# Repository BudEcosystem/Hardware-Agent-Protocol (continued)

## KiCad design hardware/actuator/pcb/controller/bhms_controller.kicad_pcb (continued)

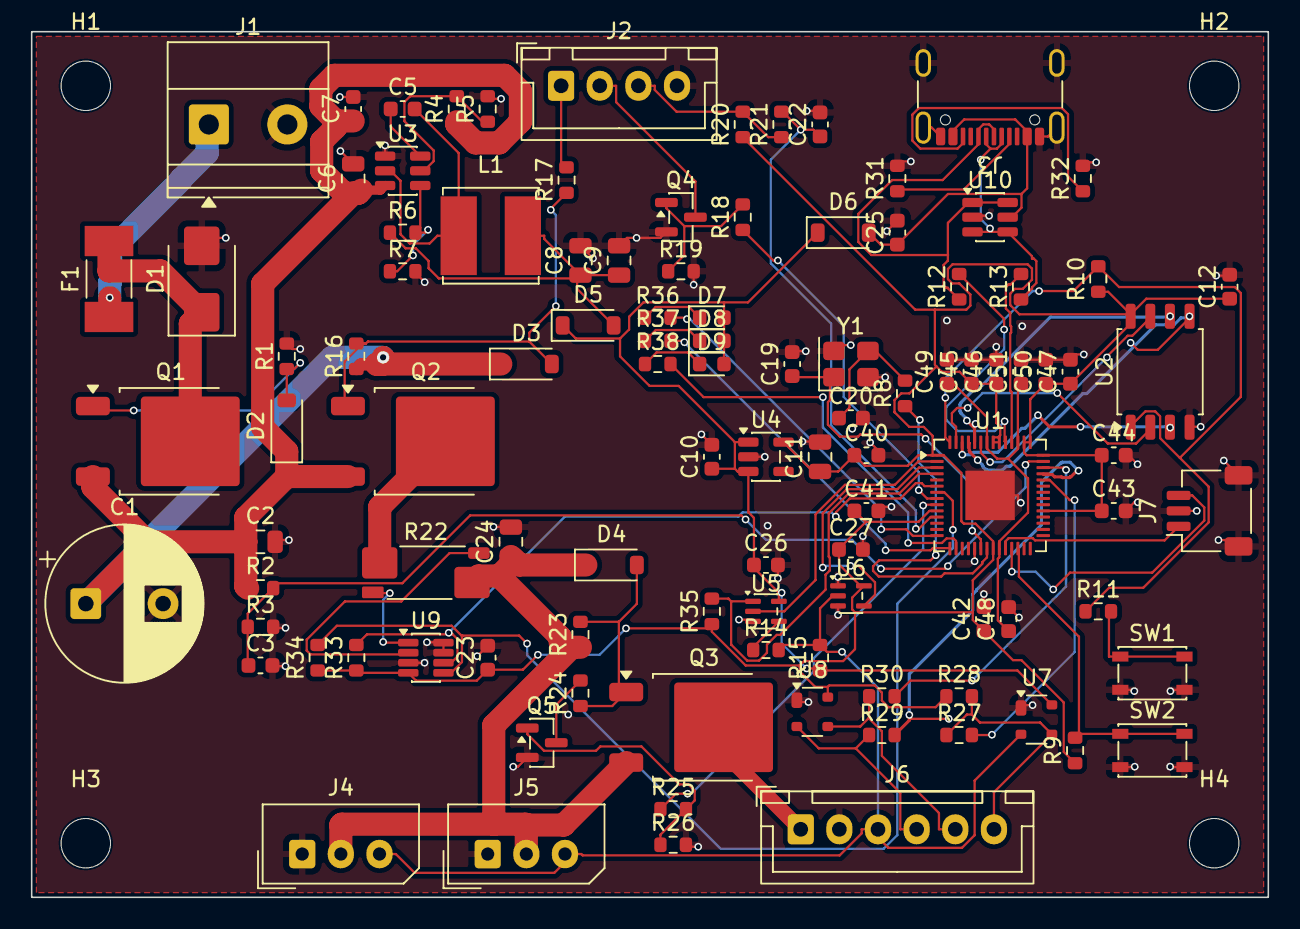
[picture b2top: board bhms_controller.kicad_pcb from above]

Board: 2 copper layers, 80.0 x 56.0 mm, 109 parts (0 on the bottom side), 69 nets.

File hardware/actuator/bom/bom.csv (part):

section,item,manufacturer,mpn,qty,unit_usd,ext_usd,price_source,notes
Arm,"Serial bus servo 12 V, 30 kg.cm, 4096-count magnetic encoder",Feetech,"STS3215 (12 V, C018 1:345)",5,18.0,90.0,"estimate (typical 2026 distributor price, not a quote)",IDs 1-5; variant code to confirm with supplier at order time
Arm,Deep-groove ball bearing 8x22x7,generic (e.g. SKF),608-2RS,4,0.5,2.0,"estimate (typical 2026 distributor price, not a quote)",shoulder and elbow shafts
Arm,"Shoulder pinion, machined steel (C45), 17T module 1.5, 14 mm face, 4 x M2 on a 14 mm circle (CNC service, drawing = cad/out/pinion_shoulder.step, committed)",CNC service (custom),cad/out/pinion_shoulder.step (committed; regenerate: python cad/build.py),1,18.0,18.0,"estimate (typical 2026 distributor price, not a quote)","ESTIMATE of a one-off turned and milled part; replaces the printed pinion (stress, design.md section 4)"
Arm,Deep-groove ball bearing 4x13x5,generic (e.g. SKF),624-2RS,3,0.6,1.8,"estimate (typical 2026 distributor price, not a quote)","2 pinion supports, wrist idler"
Arm,Deep-groove ball bearing 30x42x7,generic (e.g. SKF),6806-2RS,1,3.0,3.0,"estimate (typical 2026 distributor price, not a quote)",yaw turntable
Arm,"Hex bolt M8x70, partial thread, 8.8, zinc",generic,ISO 4014 M8x70,2,0.4,0.8,"estimate (typical 2026 distributor price, not a quote)",shoulder/elbow shafts
Arm,Nyloc nut M8,generic,ISO 10511 M8,2,0.08,0.16,"estimate (typical 2026 distributor price, not a quote)",
Arm,Washer M8 (16 mm OD),generic,ISO 7089 M8,4,0.03,0.12,"estimate (typical 2026 distributor price, not a quote)",bear on the 608 inner races only
Arm,Socket head cap screw M4x12,generic,ISO 4762 M4x12,6,0.06,0.36,"estimate (typical 2026 distributor price, not a quote)","2 pinion supports, 4 shell-to-plate"
Arm,Socket head cap screw M4x16 + nyloc nut,generic,ISO 4762 M4x16 / ISO 10511 M4,1,0.12,0.12,"estimate (typical 2026 distributor price, not a quote)",wrist idler
Arm,Washer M4 (9 mm OD),generic,ISO 7089 M4,4,0.02,0.08,"estimate (typical 2026 distributor price, not a quote)",inner-race spacers
Arm,Heat-set insert M4 x 6,generic (e.g. Ruthex),M4x8.1 RX-M4x8.1,6,0.1,0.6,"estimate (typical 2026 distributor price, not a quote)","pinion stubs, shell bosses"
Arm,Heat-set insert M3 x 5.7,generic (e.g. Ruthex),RX-M3x5.7,32,0.06,1.92,"estimate (typical 2026 distributor price, not a quote)","servo lids (5), pod lid, PCB"
Arm,Socket head cap screw M3x8,generic,ISO 4762 M3x8,32,0.04,1.28,"estimate (typical 2026 distributor price, not a quote)",
Arm,Pan head screw M2x8 (servo horn),generic,ISO 7045 M2x8,20,0.03,0.6,"estimate (typical 2026 distributor price, not a quote)","turret, pinions, wrist, flange"
Arm,"Ball spring plunger M5, 3 mm ball, stainless",generic,select at order (M5 x 12 class),1,1.5,1.5,"estimate (typical 2026 distributor price, not a quote)",bayonet detent; MPN not fixed
Arm,Heat-set insert M5,generic,RX-M5x9.5,1,0.15,0.15,"estimate (typical 2026 distributor price, not a quote)",detent plunger
Arm,"Dowel pin 3 x 6 mm, hardened",generic,ISO 8734 3x6,1,0.1,0.1,"estimate (typical 2026 distributor price, not a quote)",bayonet stop pin
Arm,"Spring-loaded contact (pogo pin), through-hole, 2.0 mm barrel, ~8 mm",Mill-Max (0906 class),select at order (Mill-Max 0906 series),6,1.2,7.2,"estimate (typical 2026 distributor price, not a quote)",flange contacts; exact MPN not fixed
Arm,"Cable 6-core 26 AWG, PUR, flexible",generic (e.g. Igus chainflex),select at order,1.5,3.0,4.5,"estimate (typical 2026 distributor price, not a quote)",metres; tool harness through the arm
Arm,"Servo extension lead 3-pin 5264, 400 mm",Feetech,accessory,2,1.5,3.0,"estimate (typical 2026 distributor price, not a quote)",chain A/B up the service loop
Arm,Cable tie 2.5 x 100 mm,generic,,10,0.02,0.2,"estimate (typical 2026 distributor price, not a quote)",
Arm,Printed part cable_clip (PETG),self-printed,cad/out/cable_clip.stl,8,0.01,0.08,"filament estimate: CAD mass model x 1.1, 22 USD/kg","0.4 g each, ~0.0 h each (estimate); orientation: flat"
Arm,Printed part flange_arm (PETG),self-printed,cad/out/flange_arm.stl,1,0.52,0.52,"filament estimate: CAD mass model x 1.1, 22 USD/kg","21.5 g each, ~0.7 h each (estimate); orientation: socket mouth up"
Arm,Printed part forearm (PETG),self-printed,cad/out/forearm.stl,1,2.666,2.67,"filament estimate: CAD mass model x 1.1, 22 USD/kg","110.2 g each, ~3.6 h each (estimate); orientation: on its side (-y face down)"
Arm,Printed part pinion_elbow (PETG),self-printed,cad/out/pinion_elbow.stl,1,0.258,0.26,"filament estimate: CAD mass model x 1.1, 22 USD/kg","10.7 g each, ~0.4 h each (estimate); orientation: horn face down, 100% infill"
Arm,Printed part servo_lid (PLA),self-printed,cad/out/servo_lid.stl,8,0.136,1.09,"filament estimate: CAD mass model x 1.1, 20 USD/kg","6.2 g each, ~0.2 h each (estimate); orientation: flat"
Arm,Printed part turret (PETG),self-printed,cad/out/turret.stl,1,2.743,2.74,"filament estimate: CAD mass model x 1.1, 22 USD/kg","113.3 g each, ~3.8 h each (estimate); orientation: disc down"
Arm,Printed part upper_arm (PETG),self-printed,cad/out/upper_arm.stl,1,3.977,3.98,"filament estimate: CAD mass model x 1.1, 22 USD/kg","164.3 g each, ~5.3 h each (estimate); orientation: on its side (+y face down), supports under clevis"
Arm,Printed part wrist_bracket (PETG),self-printed,cad/out/wrist_bracket.stl,1,0.885,0.89,"filament estimate: CAD mass model x 1.1, 22 USD/kg","36.6 g each, ~1.2 h each (estimate); orientation: bridge down"
Base & safety,Hex bolt M8x60 + hex nut (clamp screw),generic,ISO 4017 M8x60 / ISO 4032 M8,1,0.45,0.45,"estimate (typical 2026 distributor price, not a quote)",
Base & safety,Adhesive rubber foot 10 mm,3M,SJ5302,6,0.15,0.9,"estimate (typical 2026 distributor price, not a quote)",
Base & safety,"Emergency stop push button, 40 mm mushroom, turn release, 1 NC",Schneider Electric,XB4BS8445,1,25.0,25.0,"estimate (typical 2026 distributor price, not a quote)",contact block A -> E-STOP pins 1-2 (power loop)
Base & safety,Add-on contact block 1 NC,Schneider Electric,ZBE102,1,6.0,6.0,"estimate (typical 2026 distributor price, not a quote)",contact B -> pins 3-4 (sense)
Base & safety,Single-position control station enclosure,Schneider Electric,XALD01,1,12.0,12.0,"estimate (typical 2026 distributor price, not a quote)",
Base & safety,JST XH 4-pin housing + crimp contacts,JST,XHP-4 / SXH-001T-P0.6,1,0.2,0.2,"estimate (typical 2026 distributor price, not a quote)",E-stop cable
Base & safety,"Power supply 12 V 6 A, enclosed, screw terminals",Mean Well,LRS-75-12,1,20.0,20.0,"estimate (typical 2026 distributor price, not a quote)",IEC inlet cord not included
Base & safety,Cable 2-core 18 AWG + ferrules,generic,,1.0,1.5,1.5,"estimate (typical 2026 distributor price, not a quote)",metres; PSU to J1
Base & safety,Printed part base_plate (PETG),self-printed,cad/out/base_plate.stl,1,2.934,2.93,"filament estimate: CAD mass model x 1.1, 22 USD/kg","121.2 g each, ~3.9 h each (estimate); orientation: flat, bottom face down"
Base & safety,Printed part base_shell (PETG),self-printed,cad/out/base_shell.stl,1,4.063,4.06,"filament estimate: CAD mass model x 1.1, 22 USD/kg","167.9 g each, ~5.4 h each (estimate); orientation: deck down (upside down), supports in pod cutouts"
Base & safety,Printed part clamp_body (PETG),self-printed,cad/out/clamp_body.stl,1,1.564,1.56,"filament estimate: CAD mass model x 1.1, 22 USD/kg","64.6 g each, ~2.1 h each (estimate); orientation: on its side (y face down), 6 walls"
Base & safety,Printed part clamp_knob (PLA),self-printed,cad/out/clamp_knob.stl,1,0.238,0.24,"filament estimate: CAD mass model x 1.1, 20 USD/kg","10.8 g each, ~0.4 h each (estimate); orientation: flat"
Base & safety,Printed part clamp_pad (PETG),self-printed,cad/out/clamp_pad.stl,1,0.106,0.11,"filament estimate: CAD mass model x 1.1, 22 USD/kg","4.4 g each, ~0.2 h each (estimate); orientation: pad face down"
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
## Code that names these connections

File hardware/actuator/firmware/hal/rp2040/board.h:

/* BHMS Arm controller (RP2040): pin map and flash layout.
 * Source of truth: hardware/actuator/pcb/controller.py; INTERFACE.md section 1 repeats it. */
#ifndef BHMS_ARM_BOARD_H
#define BHMS_ARM_BOARD_H

#define PIN_BUS_TX 0        /* UART0 TX -> 74AHCT1G125 input A */
#define PIN_BUS_RX 1        /* UART0 RX <- 74LVC1G125 output Y (sees its own TX: echo) */
#define PIN_BUS_TXEN_N 2    /* driver enable, active low; 10 k pull-up keeps it off in reset */
#define PIN_I2C_SDA 4
#define PIN_I2C_SCL 5
#define PIN_SERVO_EN 6      /* gate of Q4; 100 k pull-down: rail off in reset */
#define PIN_TOOL_EN 7       /* gate of Q5; 100 k pull-down */
#define PIN_ESTOP_SENSE 8   /* contact B: high = pressed / open / unplugged */
#define PIN_LED_R 11        /* active low */
#define PIN_LED_G 12
#define PIN_LED_B 13
#define PIN_ADC_TOOL_ID 26  /* ADC0 */
#define PIN_ADC_AUX1 27     /* ADC1 */
#define PIN_ADC_AUX2 28     /* ADC2 */
#define PIN_ADC_VIN 29      /* ADC3: VIN = V_adc x 11 */

#define BUS_BAUD 1000000u
#define INA219_ADDR 0x40u
#define I2C_BAUD 400000u

/* Flash use (16 MiB W25Q128JV), last four 4 KiB sectors: the boot counter in the last two, the joint
 * calibration in the two before them. Both are written only with the servo rail off: a flash
 * erase/program masks interrupts, and the E-stop IRQ must not be masked while the arm is live. */
#define EPOCH_REGION_BYTES (2u * 4096u)
#define CAL_REGION_BYTES (2u * 4096u)

/* Hardware watchdog: reset the controller if the main loop stops completing. A reset drops the
 * servo rail (SERVO_EN pulls down), so an unbraked arm falls; see INTERFACE.md section 4. */
#define WATCHDOG_MS 250u
/* Around a sector erase the timeout is stretched; erases only happen with the rail off. */
#define WATCHDOG_ERASE_MS 2500u /* flash_safe_execute's lockout wait (<= 1000 ms) + a worst-case erase (~400 ms) */

#endif

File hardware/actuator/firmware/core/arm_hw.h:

/* BHMS Arm: the hardware abstraction the portable core runs on. The RP2040 port
 * (hal/rp2040) and the host simulator (sim/) each supply one const arm_hw.
 * Hooks are bounded; none may call back into the core.
 * Thread-safety: single owner (the main loop). estop_take_edge is the one hook whose
 * backing flag is written from an interrupt; the port must make that access atomic. */
#ifndef ARM_HW_H
#define ARM_HW_H

#include <stddef.h>
#include <stdint.h>

#include "arm_params.h"

#ifdef __cplusplus
extern "C" {
#endif

/* ADC channels (12-bit, 3.3 V reference). */
enum { ARM_ADC_TOOL_ID = 0, ARM_ADC_TOOL_AUX1 = 1, ARM_ADC_TOOL_AUX2 = 2, ARM_ADC_VIN = 3 };

/* Tri-colour status LED (INTERFACE.md section 7): non-zero = on. */
typedef struct arm_hw {
    void *ctx;
    uint32_t (*millis)(void *ctx);

    /* ---- Half-duplex servo bus (INTERFACE.md section 3). The port owns the driver
     * enable: bus_write drives BUS_TXEN_N low, writes, waits for the UART TX-complete
     * event, and releases the driver before returning. The RX buffer sees the echo. */
    void (*bus_flush)(void *ctx);                      /* discard pending RX bytes */
    void (*bus_write)(void *ctx, const uint8_t *buf, size_t n);
    /* Read up to n bytes; waits at most timeout_us for each missing byte. Returns the
     * number of bytes read (less than n on timeout). */
    size_t (*bus_read)(void *ctx, uint8_t *buf, size_t n, uint32_t timeout_us);

    /* ---- Power and E-stop GPIO (INTERFACE.md sections 2 and 4). */
    void (*servo_en)(void *ctx, int on);   /* GPIO6 */
    void (*tool_en)(void *ctx, int on);    /* GPIO7 */
    int (*estop_sense)(void *ctx);         /* GPIO8: 1 = pressed / open / unplugged */
    /* Latched rising edge of GPIO8 (set from the IRQ, which has already cleared SERVO_EN);
     * returns nonzero once per edge and clears it. */
    int (*estop_take_edge)(void *ctx);

    uint16_t (*adc_read)(void *ctx, uint8_t channel);

    /* INA219 raw registers: bus voltage (0x02) and current (0x04). Returns 0 on success. */
    int (*ina_read)(void *ctx, uint16_t *bus_reg, int16_t *current_reg);

    void (*led)(void *ctx, uint8_t r, uint8_t g, uint8_t b);

    /* ---- Optional (NULL when the platform has none). */
    /* Nonzero when the last reset was caused by the watchdog. */
    int (*watchdog_reset)(void *ctx);
    /* Persistent joint calibration: load returns 1 when a stored calibration exists. save
     * returns 0 once it is durable; it may mask interrupts for tens of ms, so the core calls it
     * only with the servo rail off. */
    int (*cal_load)(void *ctx, arm_cal *cal);
    int (*cal_save)(void *ctx, const arm_cal *cal);
} arm_hw;

#ifdef __cplusplus
}
#endif
#endif
